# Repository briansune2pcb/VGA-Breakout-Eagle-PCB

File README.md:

# VGA-Breakout-Eagle-PCB
VGA Breakout PCB

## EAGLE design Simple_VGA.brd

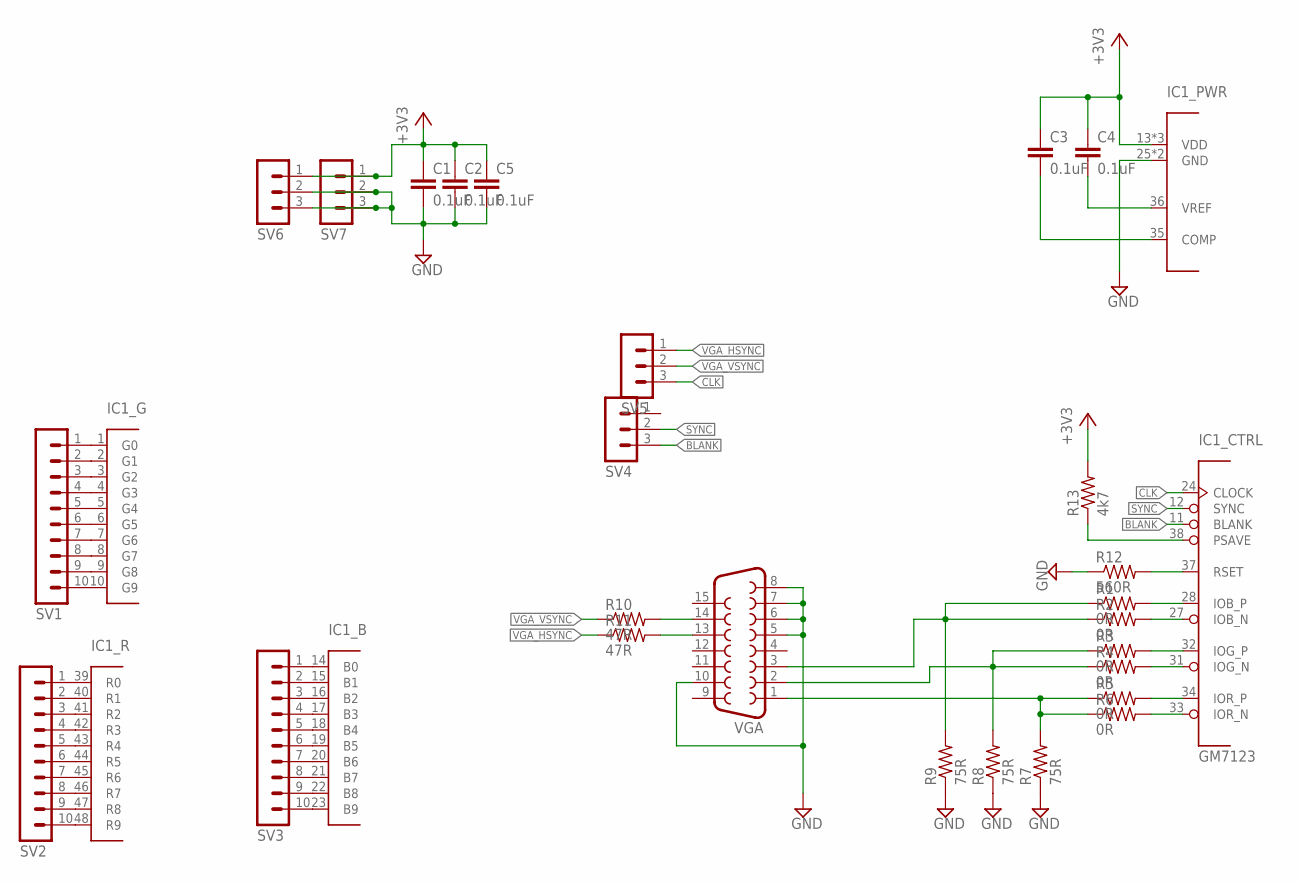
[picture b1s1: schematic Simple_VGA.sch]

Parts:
C1, C2, C3, C4, C5: 0.1uF; C1206
IC1: GM7123; TQFP48
R1, R2, R3, R4, R5, R6: 0R; R1206
R7, R8, R9: 75R; R1206
R10, R11: 47R; R1206
R12: 560R; R1206
R13: 4k7; R1206
SV1, SV2, SV3: MA10-1
SV4, SV5, SV6, SV7: MA03-1
VGA: F15HDH; HDF15H

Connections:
+3V3: C1.1, C2.1, C3.1, C4.1, C5.1, IC1.13 (VDD), IC1.29 (VDD), IC1.30 (VDD), R13.2, SV6.1, SV7.1
BLANK: IC1.11 (BLANK), SV4.3
CLK: IC1.24 (CLOCK), SV5.3
GND: C1.2, C2.2, C5.2, IC1.25 (GND), IC1.26 (GND), R7.1, R8.1, R9.1, R12.1, SV6.2, SV6.3, SV7.2, SV7.3, VGA.5, VGA.6, VGA.7, VGA.8, VGA.10
unnamed: IC1.1 (G0), SV1.1
unnamed: IC1.2 (G1), SV1.2
unnamed: IC1.3 (G2), SV1.3
unnamed: IC1.4 (G3), SV1.4
unnamed: IC1.5 (G4), SV1.5
unnamed: IC1.6 (G5), SV1.6
unnamed: IC1.7 (G6), SV1.7
unnamed: IC1.8 (G7), SV1.8
unnamed: IC1.9 (G8), SV1.9
unnamed: IC1.10 (G9), SV1.10
unnamed: IC1.39 (R0), SV2.1
unnamed: IC1.40 (R1), SV2.2
unnamed: IC1.41 (R2), SV2.3
unnamed: IC1.42 (R3), SV2.4
unnamed: IC1.43 (R4), SV2.5
unnamed: IC1.44 (R5), SV2.6
unnamed: IC1.45 (R6), SV2.7
unnamed: IC1.46 (R7), SV2.8
unnamed: IC1.47 (R8), SV2.9
unnamed: IC1.48 (R9), SV2.10
unnamed: IC1.14 (B0), SV3.1
unnamed: IC1.15 (B1), SV3.2
unnamed: IC1.16 (B2), SV3.3
unnamed: IC1.17 (B3), SV3.4
unnamed: IC1.18 (B4), SV3.5
unnamed: IC1.19 (B5), SV3.6
unnamed: IC1.20 (B6), SV3.7
unnamed: IC1.21 (B7), SV3.8
unnamed: IC1.22 (B8), SV3.9
unnamed: IC1.23 (B9), SV3.10
unnamed: IC1.28 (IOB_P), R1.2
unnamed: IC1.27 (IOB_N), R2.2
unnamed: IC1.32 (IOG_P), R3.2
unnamed: IC1.31 (IOG_N), R4.2
unnamed: IC1.34 (IOR_P), R5.2
unnamed: IC1.33 (IOR_N), R6.2
unnamed: R5.1, R6.1, R7.2, VGA.1
unnamed: R3.1, R4.1, R8.2, VGA.2
unnamed: R1.1, R2.1, R9.2, VGA.3
unnamed: IC1.37 (RSET), R12.2
unnamed: IC1.38 (PSAVE), R13.1
unnamed: C4.2, IC1.36 (VREF)
unnamed: C3.2, IC1.35 (COMP)
SYNC: IC1.12 (SYNC), SV4.2
VGA_HSYNC: R11.1, SV5.1
VGA_HSYNC2: R11.2, VGA.13
VGA_VSYNC: R10.1, SV5.2
VGA_VSYNC2: R10.2, VGA.14

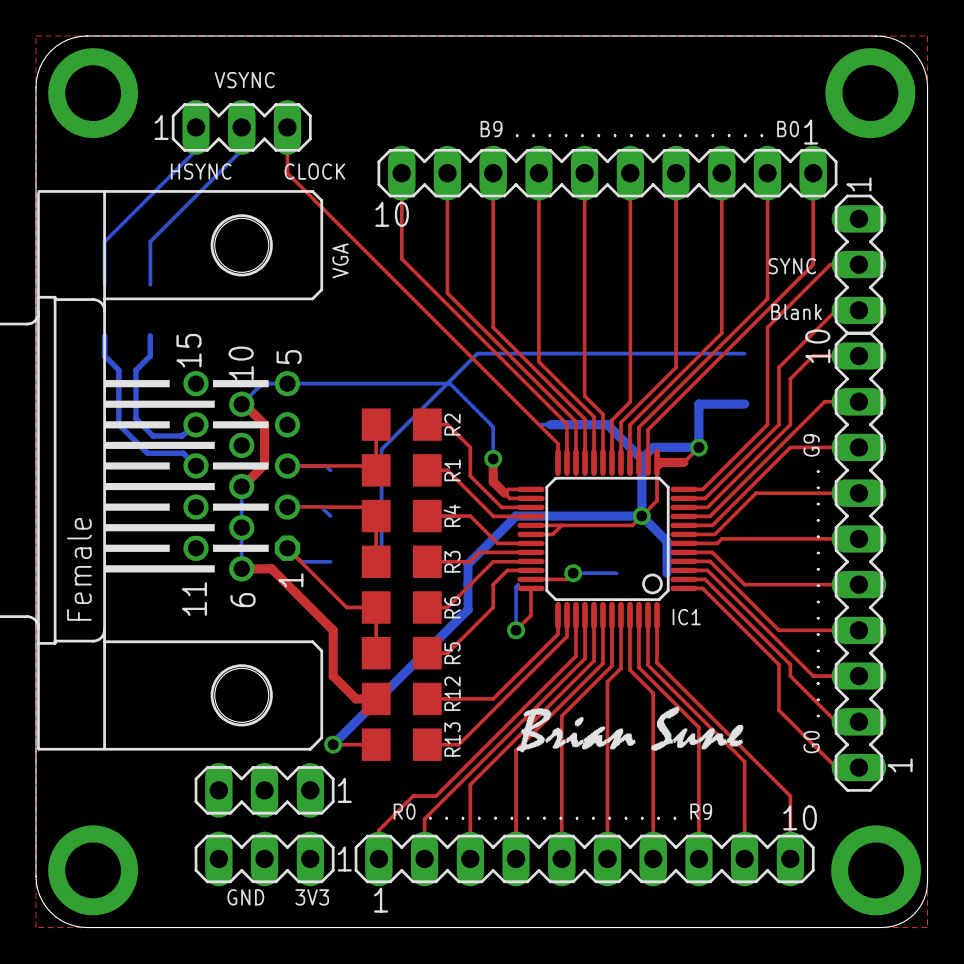
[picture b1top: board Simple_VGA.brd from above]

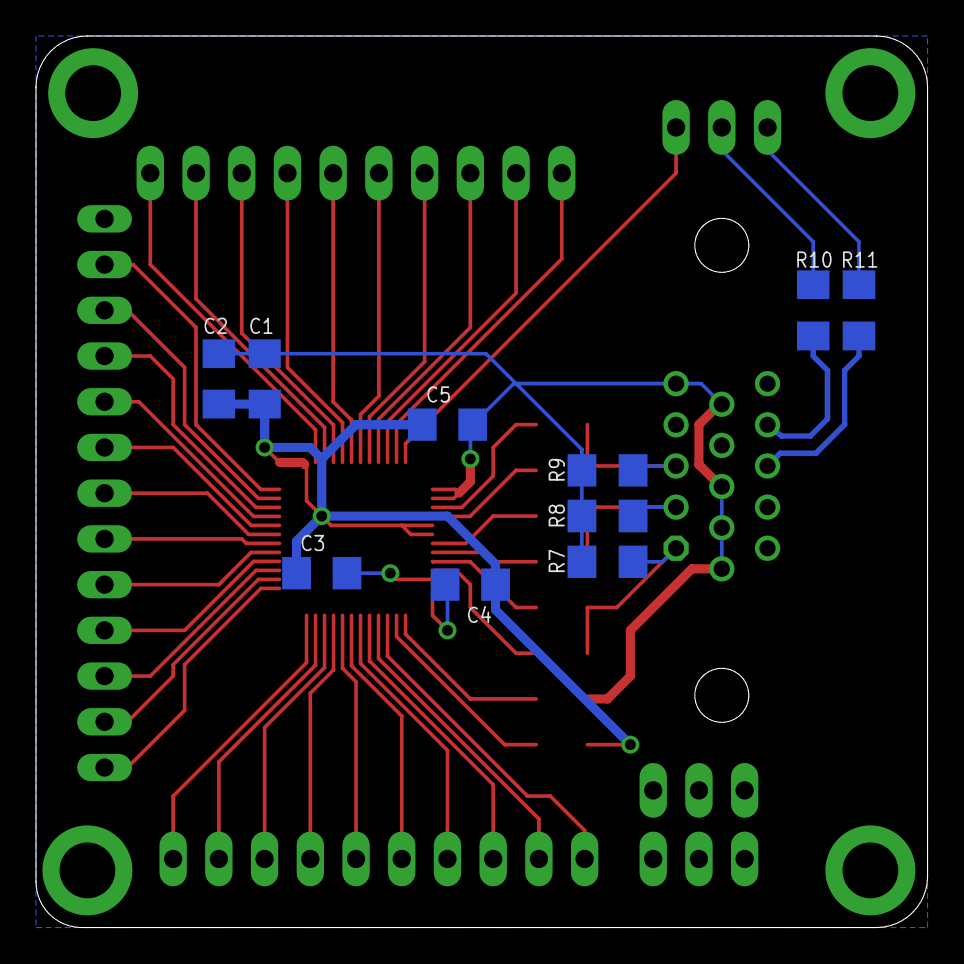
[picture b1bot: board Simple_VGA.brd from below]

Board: 2 copper layers, 49.5 x 49.5 mm, 27 parts (10 on the bottom side), 52 nets.
